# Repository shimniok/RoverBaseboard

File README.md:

RoverBaseboard is a baseboard for use in autonomous rover projects. It supports mbed LPC1768, LPCXpresso,
and compatible pinouts. This same baseboard design was used on my 1986 Jeep Grand Wagoneer, "Troubled Child"
when it won 1st place, "Doping" class, in the 2014 Sparkfun AVC.

The baseboard breaks out UARTs, I2C, analog, digital, PWM. Each I2C and UART "port" also provides 5V, 3.3V, GND
pins.  It features a microSD card socket and an onboard 3.3V external LDO regulator.

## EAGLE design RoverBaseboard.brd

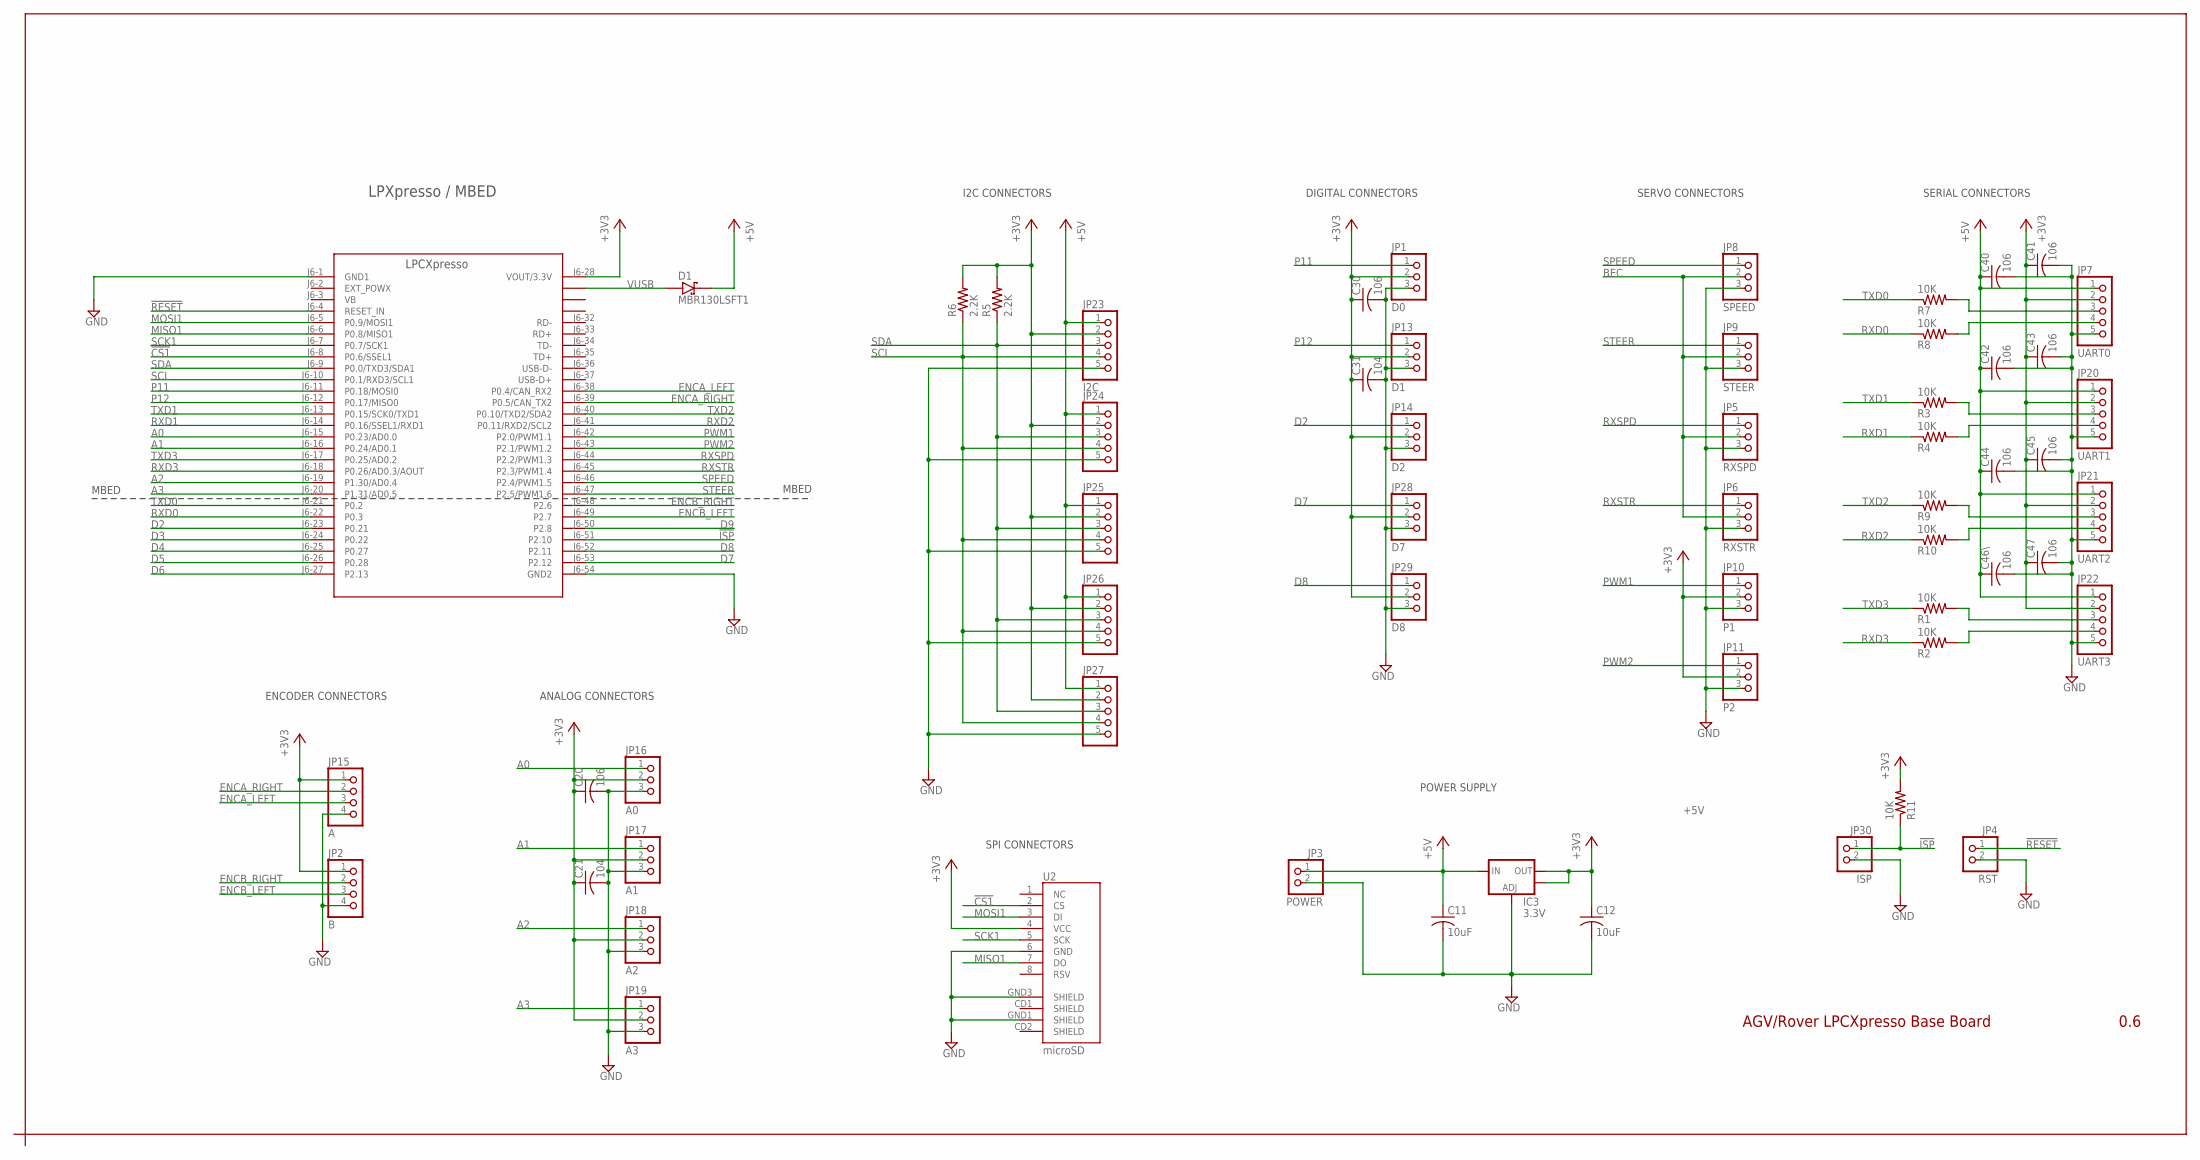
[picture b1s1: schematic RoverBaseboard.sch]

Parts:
C11, C12: 10uF; C1206
C20, C30, C40, C41, C42, C43, C44, C45, C46\, C47: 106; C0603
C21, C31: 104; C0603
D1: MBR130LSFT1; SOD123FL
IC3: 3.3V; SOT223
JP1: D0; 1X03-S
JP2: B; 1X04-S
JP3: POWER; 1X02-S
JP4: RST; 1X02-S
JP5: RXSPD; 1X03-S
JP6: RXSTR; 1X03-S
JP7: UART0; 1X05-S
JP8: SPEED; 1X03-S
JP9: STEER; 1X03-S
JP10: P1; 1X03-S
JP11: P2; 1X03-S
JP13: D1; 1X03-S
JP14: D2; 1X03-S
JP15: A; 1X04-S
JP16: A0; 1X03-S
JP17: A1; 1X03-S
JP18: A2; 1X03-S
JP19: A3; 1X03-S
JP20: UART1; 1X05-S
JP21: UART2; 1X05-S
JP22: UART3; 1X05-S
JP23: I2C; 1X05-S
JP24, JP25, JP26, JP27: PINHD-1X05_2.54-S; 1X05-S
JP28: D7; 1X03-S
JP29: D8; 1X03-S
JP30: ISP; 1X02-S
R1, R2, R3, R4, R7, R8, R9, R10, R11: 10K; R0603; MPN WCR0805-220RFI
R5, R6: 2.2K; R0603
U2: microSD; MICRO-SD-SOCKET-PP
U$1: LPCXPRESSO; LPCXPRESSO_NO_PAD

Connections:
!CS1: U2.2 (CS), U$1.J6-8 (P0.6/SSEL1)
!ISP: JP30.1, R11.1, U$1.J6-51 (P2.10)
!RESET: JP4.1, U$1.J6-4 (RESET_IN)
+3V3: C12.1, C20.1, C21.1, C30.1, C31.1, C41.1, C43.1, C45.1, C47.1, IC3.2 (OUT), IC3.4 (OUT), JP1.2, JP2.1, JP7.2, JP10.2, JP11.2, JP13.2, JP14.2, JP15.1, JP16.2, JP17.2, JP18.2, JP19.2, JP20.2, JP21.2, JP22.2, JP23.2, JP24.2, JP25.2, JP26.2, JP27.2, JP28.2, JP29.2, R5.2, R6.2, R11.2, U2.4 (VCC), U$1.J6-28 (VOUT/3.3V)
+5V: C11.1, C40.1, C42.1, C44.1, C46\.1, D1.C, IC3.3 (IN), JP3.1, JP7.1, JP20.1, JP21.1, JP22.1, JP23.1, JP24.1, JP25.1, JP26.1, JP27.1
A0: JP16.1, U$1.J6-15 (P0.23/AD0.0)
A1: JP17.1, U$1.J6-16 (P0.24/AD0.1)
A2: JP18.1, U$1.J6-19 (P1.30/AD0.4)
A3: JP19.1, U$1.J6-20 (P1.31/AD0.5)
BEC: JP5.2, JP6.2, JP8.2, JP9.2
D2: JP14.1, U$1.J6-23 (P0.21)
D3: U$1.J6-24 (P0.22)
D4: U$1.J6-25 (P0.27)
D5: U$1.J6-26 (P0.28)
D6: U$1.J6-27 (P2.13)
D7: JP28.1, U$1.J6-53 (P2.12)
D8: JP29.1, U$1.J6-52 (P2.11)
D9: U$1.J6-50 (P2.8)
ENCA_LEFT: JP15.3, U$1.J6-38 (P0.4/CAN_RX2)
ENCA_RIGHT: JP15.2, U$1.J6-39 (P0.5/CAN_TX2)
ENCB_LEFT: JP2.3, U$1.J6-49 (P2.7)
ENCB_RIGHT: JP2.2, U$1.J6-48 (P2.6)
GND: C11.2, C12.2, C20.2, C21.2, C30.2, C31.2, C40.2, C41.2, C42.2, C43.2, C44.2, C45.2, C46\.2, C47.2, IC3.1 (ADJ), JP1.3, JP2.4, JP3.2, JP4.2, JP5.3, JP6.3, JP7.5, JP8.3, JP9.3, JP10.3, JP11.3, JP13.3, JP14.3, JP15.4, JP16.3, JP17.3, JP18.3, JP19.3, JP20.5, JP21.5, JP22.5, JP23.5, JP24.5, JP25.5, JP26.5, JP27.5, JP28.3, JP29.3, JP30.2, U2.6 (GND), U2.GND1 (SHIELD), U2.GND3 (SHIELD), U$1.J6-1 (GND1), U$1.J6-54 (GND2)
MISO1: U2.7 (DO), U$1.J6-6 (P0.8/MISO1)
MOSI1: U2.3 (DI), U$1.J6-5 (P0.9/MOSI1)
unnamed: JP22.3, R1.2
unnamed: JP22.4, R2.2
unnamed: JP7.3, R7.2
unnamed: JP7.4, R8.2
unnamed: JP20.3, R3.2
unnamed: JP20.4, R4.2
unnamed: JP21.3, R9.2
unnamed: JP21.4, R10.2
P11: JP1.1, U$1.J6-11 (P0.18/MOSI0)
P12: JP13.1, U$1.J6-12 (P0.17/MISO0)
PWM1: JP10.1, U$1.J6-42 (P2.0/PWM1.1)
PWM2: JP11.1, U$1.J6-43 (P2.1/PWM1.2)
RXD0: R8.1, U$1.J6-22 (P0.3)
RXD1: R4.1, U$1.J6-14 (P0.16/SSEL1/RXD1)
RXD2: R10.1, U$1.J6-41 (P0.11/RXD2/SCL2)
RXD3: R2.1, U$1.J6-18 (P0.26/AD0.3/AOUT)
RXSPD: JP5.1, U$1.J6-44 (P2.2/PWM1.3)
RXSTR: JP6.1, U$1.J6-45 (P2.3/PWM1.4)
SCK1: U2.5 (SCK), U$1.J6-7 (P0.7/SCK1)
SCL: JP23.4, JP24.4, JP25.4, JP26.4, JP27.4, R6.1, U$1.J6-10 (P0.1/RXD3/SCL1)
SDA: JP23.3, JP24.3, JP25.3, JP26.3, JP27.3, R5.1, U$1.J6-9 (P0.0/TXD3/SDA1)
SPEED: JP8.1, U$1.J6-46 (P2.4/PWM1.5)
STEER: JP9.1, U$1.J6-47 (P2.5/PWM1.6)
TXD0: R7.1, U$1.J6-21 (P0.2)
TXD1: R3.1, U$1.J6-13 (P0.15/SCK0/TXD1)
TXD2: R9.1, U$1.J6-40 (P0.10/TXD2/SDA2)
TXD3: R1.1, U$1.J6-17 (P0.25/AD0.2)
VUSB: D1.A, U$1.J6-31

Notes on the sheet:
SERVO CONNECTORS
SPI CONNECTORS
I2C CONNECTORS
SERIAL CONNECTORS
AGV/Rover LPCXpresso Base Board
0.6
ANALOG CONNECTORS
DIGITAL CONNECTORS
MBED
ENCODER CONNECTORS
LPXpresso / MBED
POWER SUPPLY

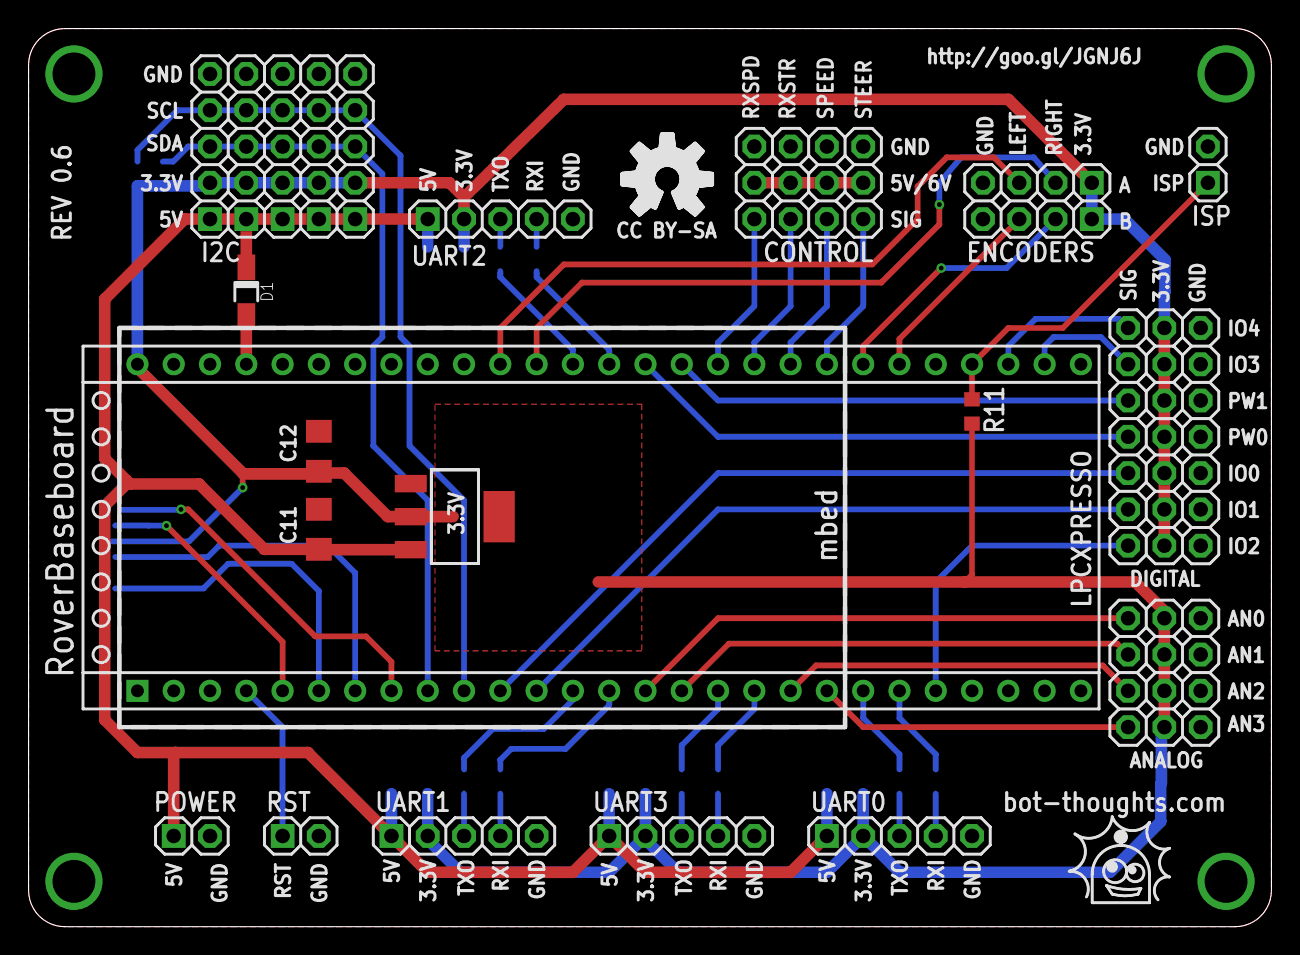
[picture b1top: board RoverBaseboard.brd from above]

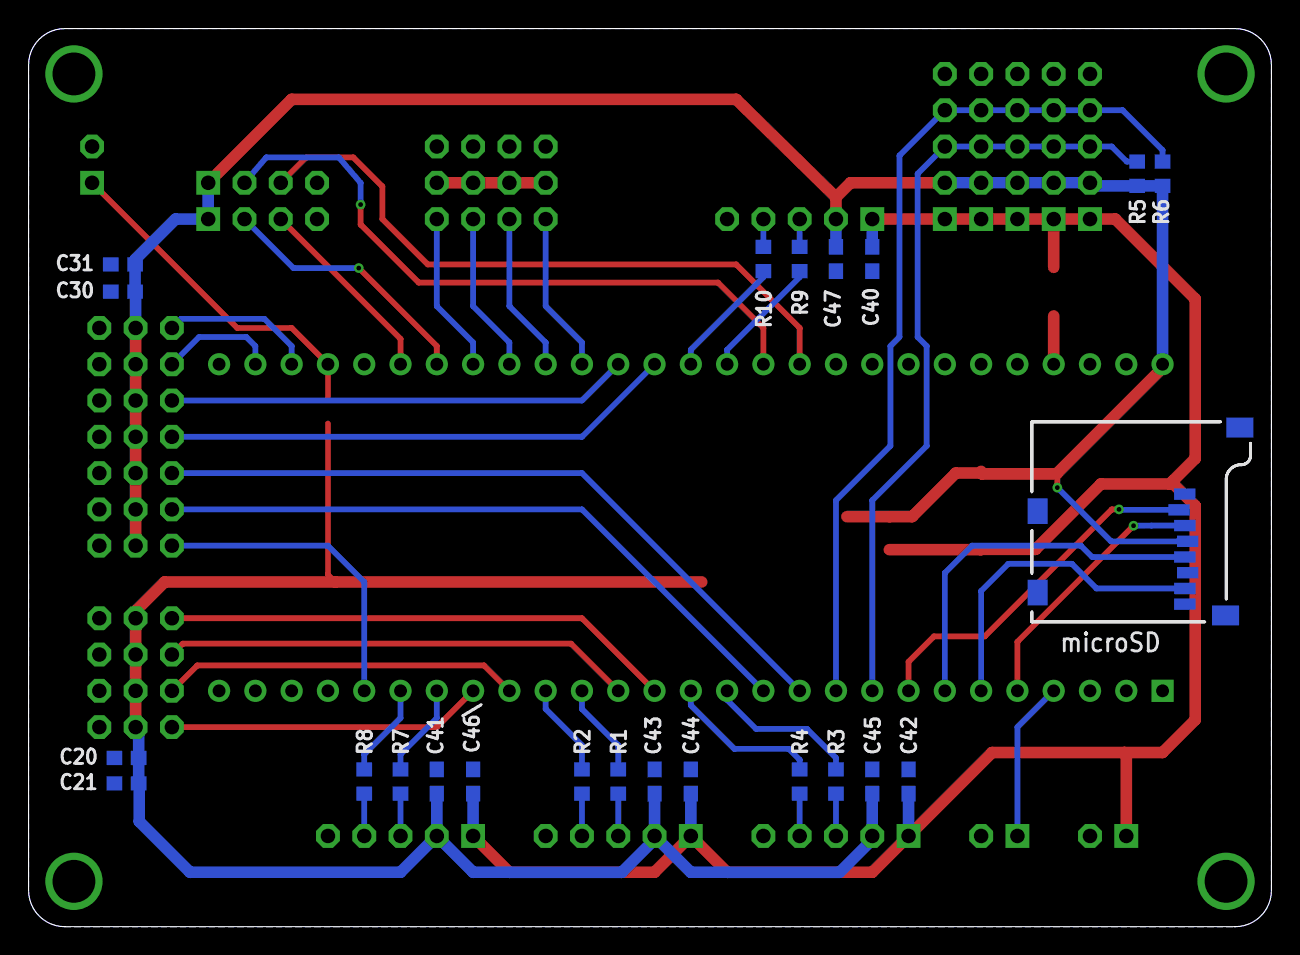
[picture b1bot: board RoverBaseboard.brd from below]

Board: 2 copper layers, 87.0 x 62.9 mm, 58 parts (23 on the bottom side), 48 nets.

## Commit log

2013-11-04 Trying to fix repository
2013-11-05 Bugfix to supply--3.3V regulator now feeds LPCXpresso. Minor tweaks. Powering analog ports more directly. Rerouted power. Moved power pins to align to 0.1" spacing. Heat sink now connected to 3V3 out.
2013-11-22 Change to LDO regulator, added port labels for digital, analog, encoders, change cap values.
2013-11-22 Renamed VBEC net
2013-11-22 Added ISP pushbutton and pullup
2014-02-04 Added ISP pin headers, revised power supply selection layout, added pin header for selecting external 5VIN in addition to selections for 5V or 6V BEC. Renumbered capacitors. Verified cap voltages, et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
2014-02-04 Added documentation to schematic
2014-03-11 Revised net names to better reflect encoders. Changed pin header labels to better reflect function.
2014-05-16 Updated pin names, removed BEC>5V regulator, moved VIN pins back to original spot.
2014-05-16 Added gerber files and zip
2015-05-08 Added README and LICENSE files.
2021-02-11 added diode for VUSB/5V so both can be connected safely

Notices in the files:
RoverBaseboard.brd:
CC BY-SA
